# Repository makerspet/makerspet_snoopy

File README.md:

# Snoopy pet robot

An open-source 300mm DIY 3D-printable pet robot compatible with [Kaia.ai](https://kaia.ai) software [platform](https://github.com/kaiaai/).

Snoopy was designed in Fusion 360 in 05/2023 and printed using a Voron 2.4r2 350mm.

3D print, build, run and mod your own home pet robot! Please learn more at [Maker's Pet](https://makerspet.com).

## Features
- room mapping using a 360-degree laser distance sensor (ROS2-based).
- fully autonomous navigation (ROS2-based).
- code your character, skills (work in progress)
- 3D-printable, 300mm round base
- A smartphone or a 7" tablet acts as a color camera, head display.
- Arduino ESP32 micro-controller.
- optional: 2 bumpers, 4 bumper sensors, 5 cliff sensors.

## Assembly instructions video (Loki, Fido models)

## PC, firmware setup instructions video

## Bring-up instructions video

## 3D printing instructions

## Arduino ESP32 breakout board setup instructions

## Instructions and files
- 3D printing [STL](https://github.com/makerspet/3d_models/tree/main/snoopy_300mm/stl), [3MF](https://github.com/makerspet/3d_models/tree/main/snoopy_300mm/3mf)
- Arduino ESP32 [firmware](https://github.com/kaiaai/firmware)
- PC end user and developer [setup](https://github.com/kaiaai/docker)
- KiCad [schematic, PCB](https://github.com/makerspet/pcb)
- Software setup, configuration [instructions](https://www.youtube.com/playlist?list=PLOSXKDW70aR8SA16wTB0ou9ClKhv7micy)
- Fusion 360 3D CAD [design files](https://github.com/makerspet/3d_models/tree/main/snoopy_300mm/fusion360)
- ROS2 software mod [instructions](https://github.com/makerspet/makerspet_loki/tree/main/urdf)

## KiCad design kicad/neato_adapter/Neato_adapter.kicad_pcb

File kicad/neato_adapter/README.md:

# Adapter PCB for LDS02RR laser distance scanner

Connect Neato XV/Botvac LDS to Arduino to capture laser distance data.

This PCB implements PWM motor control for Neato XV/Botvac LDS. Find
sample Arduino ESP32 firmware code [here](https://github.com/kaiaai/LDS02RR_ESP32).

## Files
- [schematic PDF](output/Neato_adapter_schematic.pdf)
- [BoM .CSV](output/Neato_adapter_BOM.csv), [BoM .XML](output/Neato_adapter_BOM.xml)
- [Gerber .ZIP](output/Neato_adapter_gerber.zip)
- [3D model .STEP](output/Neato_adapter.step)
- KiCAD schematic, layout - in this folder

## Top

## Bottom

# Change log

## v0.1.0
- initial prototype
- optional LM2596 voltage regulator module provides 3.3V to motor

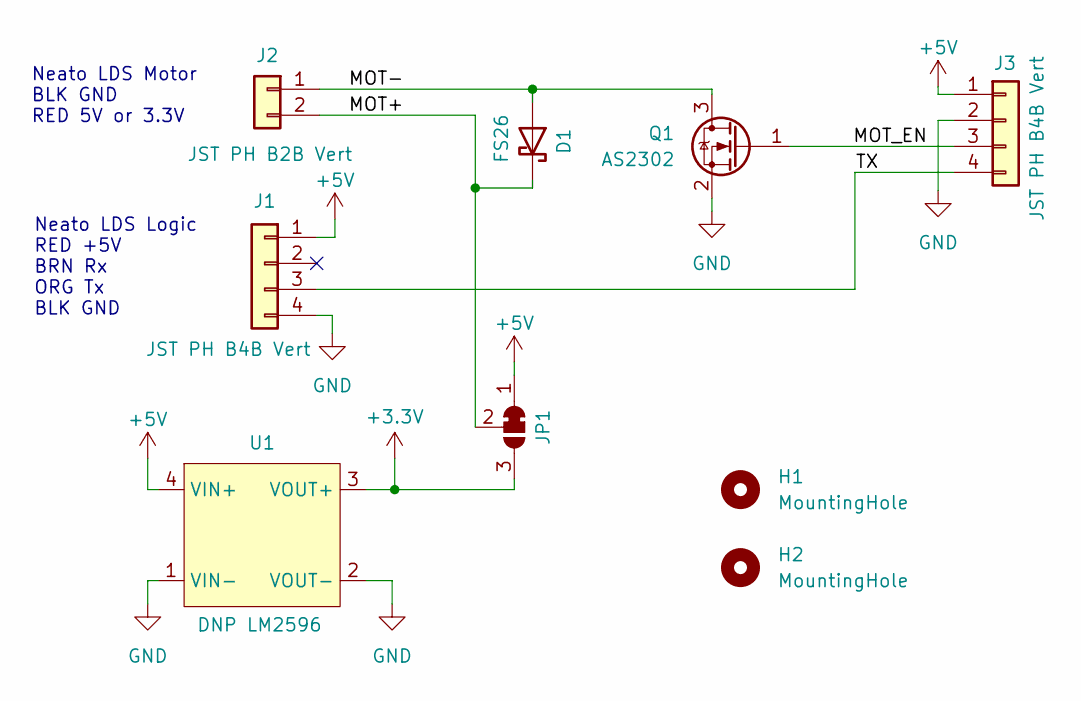
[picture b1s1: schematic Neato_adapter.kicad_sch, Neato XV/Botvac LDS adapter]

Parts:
D1: FS26; D_SOD-123F
H1, H2: MountingHole; MountingHole_3.2mm_M3
J1, J3: JST PH B4B Vert; JST_PH_B4B-PH-K_1x04_P2.00mm_Vertical
J2: JST PH B2B Vert; JST_PH_B2B-PH-K_1x02_P2.00mm_Vertical
JP1: SolderJumper_3_Bridged12; SolderJumper-3_P1.3mm_Bridged12_RoundedPad1.0x1.5mm_NumberL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
Q1: AS2302; SOT-23
U1: DNP LM2596; LM2596 Module

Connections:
+3.3V: JP1.3 (B), U1.3 (VOUT+)
+5V: J1.1, J3.1, JP1.1 (A), U1.4 (VIN+)
/MOT+: D1.1 (K), J2.2, JP1.2 (C)
/MOT-: D1.2 (A), J2.1, Q1.3 (D)
/MOT_EN: J3.3, Q1.1 (G)
/TX: J1.3, J3.4
GND: J1.4, J3.2, Q1.2 (S), U1.1 (VIN-), U1.2 (VOUT-)

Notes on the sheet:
Neato LDS Logic RED +5V BRN Rx ORG Tx BLK GND
Neato LDS Motor BLK GND RED 5V or 3.3V

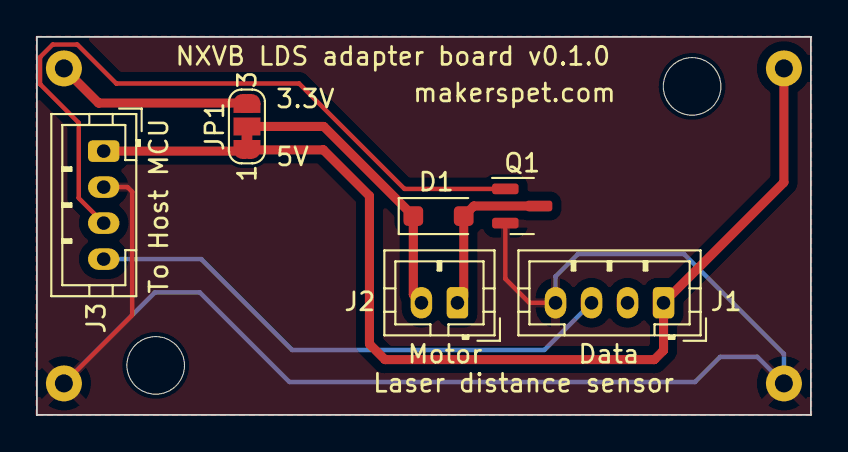
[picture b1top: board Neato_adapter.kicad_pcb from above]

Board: 2 copper layers, 43.0 x 21.0 mm, 9 parts (1 on the bottom side), 7 nets.

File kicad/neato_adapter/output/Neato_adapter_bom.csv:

"Source:","C:\Users\ilya\git\snoopy\kicad\neato_adapter\Neato_adapter.kicad_sch"
"Date:","1/16/2024 11:24:24 PM"
"Tool:","Eeschema 7.0.9"
"Generator:","C:\Program Files\KiCad\7.0\bin\scripting\plugins/bom_csv_grouped_by_value_with_fp.py"
"Component Count:","6"
"Ref","Qnty","Value","Cmp name","Footprint","Description","Vendor","DNP"
"D1","1","FS26","D_Schottky","Diode_SMD:D_SOD-123F","Schottky diode","",""
"J1, J3","2","JST PH B4B Vert","Conn_01x04","Connector_JST:JST_PH_B4B-PH-K_1x04_P2.00mm_Vertical","Generic connector, single row, 01x04, script generated (kicad-library-utils/schlib/autogen/connector/)","",""
"J2","1","JST PH B2B Vert","Conn_01x02","Connector_JST:JST_PH_B2B-PH-K_1x02_P2.00mm_Vertical","Generic connector, single row, 01x02, script generated (kicad-library-utils/schlib/autogen/connector/)","",""
"Q1","1","AS2302","BSS123","Package_TO_SOT_SMD:SOT-23","0.17A Id, 100V Vds, N-Channel MOSFET, SOT-23","",""
"U1","1","DNP LM2596","LM2596 Module","Makerspet:LM2596 Module","DC-DC voltage regulator module","",""

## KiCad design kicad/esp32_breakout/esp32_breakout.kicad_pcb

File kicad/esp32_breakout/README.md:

# Arduino ESP32 Breakout PCB for Maker's Pet robots

## Files
- [schematic PDF](output/esp32_breakout_schematic.pdf)
- [BoM .CSV](output/esp32_breakout_bom.csv), [BoM .XML](output/esp32_breakout_bom.xml)
- [Gerber .ZIP](output/esp32_breakout_gerber.zip)
- [3D model .STEP](output/esp32_breakout.step)
- KiCAD schematic, layout - in this folder

## Top

## Bottom

# Change log

## v1.1.0
- 3D-printed board enclosure to prevent accidental 24V shorts
- merged GPIO, US-100 sonar headers into a single 12-pin header

## v1.0.1
- fixed GPIO header footprint

## v1.0.0
- changed voltage regulator to LM2596 DC-DC module
  - unlike other low-cost DC-DC modules, LM2596 has built-in output current limit, short and thermal protection
  - LM2596 can accept up to 40V input as a measure for input overvoltage protection
  - Note that motors are not protected from overvoltage
- reduced the number of extension connectors to 2 from 3
  - for two Raspberry Pi Pico extension modules - one for the robot's head, one for the robot's body
- fixed extension interface I2C resistors
- replaced power connector with XT30 instead of Deans T-Plug
  - T-Plug requires uncomfortably too much insertion force
- added 24V input reverse polarity protection using a Schotki diode
- added 24 input overcurrent protection using a 2A one-time fuse
- removed support for LDS that don't control motor on/off
  - such LDS models are rare; this can be re-added later if needed
- added an ESP32 5V power supply protection Schottky diode
  - to prevent ESP32's USB back-charging the LM2596 voltage regulator
  - I don't believe this diode is necessary for LM2596 combined with built-in ESP32 Schottky diode, but let's have it just in case
- removed the 3-pin laser header and merged its GPIO to the GPIO connector
  - let's keep the ESP32 modules as a "platform" and put custom functionality on the Raspberry Pi Pico modules
  - customizing the ESP32 code to add custom functionality can easily slow down the ESP32 code that is optimized for speed and thus create issues
- changed the GPIO connector to single row from dual rows
  - to reduce the board size
  - I don't recommend using ESP32 GPIO because this requires modifying ESP32 code, which can easily slow down or break the ESP32 firmware.
    ESP32 is already pretty busy with ROS2 and WiFi low-latency communications.
  - please add custom functionality (sensors, servos, lights) to the Raspberry Pi Pico extension modules, not ESP32
- added US-100 ultrasonic range sensor
  - let's use US-100 instead of the popular HC-04 because HC-04 can "hang", sometimes requiring a power cycle.
    HC-04 performance varies depending on its manufacturer and some HC-04 modules are plain unusable.
    US-100 communicates with ESP32 using 9600 baud serial (less work for the ESP32 compared to HC-04)
    and offers a considerably better and consistent measurement quality. US-100 costs somewhat more compared to HC-04.
- fixed battery voltage sensing ADC resistor divider values
- removed battery charging connector
  - the charging connection depends on the battery BMS, therefore the charger/dock should connect to the battery instead of the board
- added silkscreens: makerspet.com, board name and version

## v0.1 PCB prototype
- Deans T-Plug type battery connector
- barrel-type battery charger connector
- US-100 ultrasonic distance sensor header
- laser pointer header
- miscellaneous unused GPIO header
- battery voltage sensing using ESP32 ADC
- PCB mounting holes
- 3 I2C extension connectors
- power-on switch
- LDS connector supporting a large variety of laser distance scanners, including those that don't control motor on/off
- fixed motors "kicking" during power-up
  - reassigned some motor control signals to ESP32 GPIO that do not toggle during ESP32 power-up boot
- mini560 Pro 5V DC-DC voltage regulator module

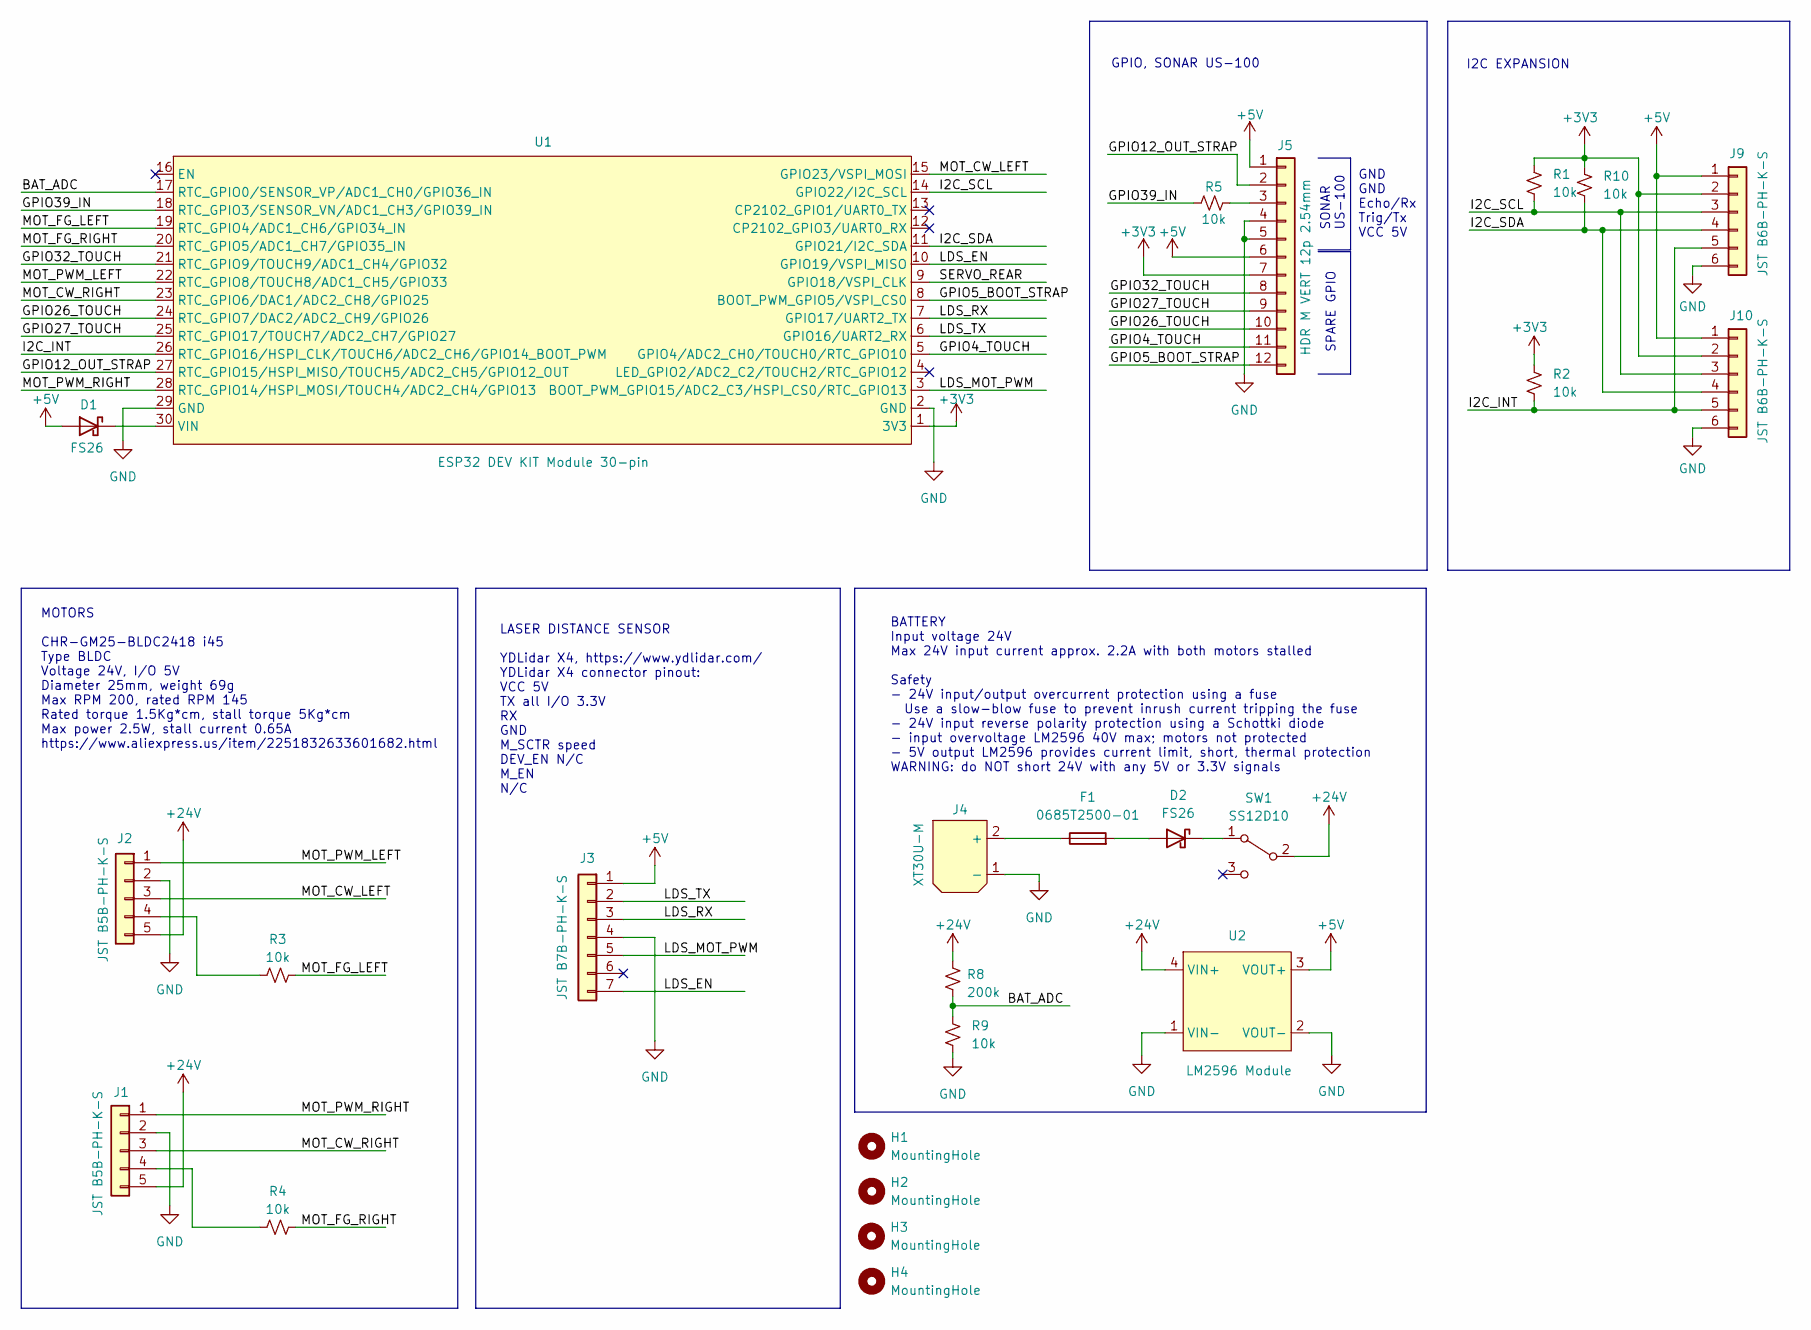
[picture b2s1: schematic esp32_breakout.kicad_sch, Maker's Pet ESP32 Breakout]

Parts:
D1, D2: FS26; D_SOD-123F
F1: 0685T2500-01; Fuse_1206_3216Metric
H1, H2, H3, H4: MountingHole; MountingHole_3.2mm_M3
J1, J2: JST B5B-PH-K-S; JST_PH_B5B-PH-K_1x05_P2.00mm_Vertical
J3: JST B7B-PH-K-S; JST_PH_B7B-PH-K_1x07_P2.00mm_Vertical
J4: XT30U-M; AMASS_XT30U-F_1x02_P5.0mm_Vertical
J5: HDR M VERT 12p 2.54mm; PinSocket_1x12_P2.54mm_Vertical
J9, J10: JST B6B-PH-K-S; JST_PH_B6B-PH-K_1x06_P2.00mm_Vertical
R1, R2, R3, R4, R5, R9, R10: 10k; R_0603_1608Metric
R8: 200k; R_0603_1608Metric
SW1: SS12D10; SWITCH
U1: ESP32 DEV KIT Module 30-pin; ESP-32
U2: LM2596 Module

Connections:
+3V3: J5.7, J9.2, J10.2, R1.1, R2.1, R10.1, U1.1 (3V3)
+5V: D1.2 (A), J3.1, J5.1, J5.6, J9.1, J10.1, U2.3 (VOUT+)
+24V: J1.5, J2.5, R8.2, SW1.2 (B), U2.4 (VIN+)
/BAT_ADC: R8.1, R9.2, U1.17 (RTC_GPIO0/SENSOR_VP/ADC1_CH0/GPIO36_IN)
/GPIO4_TOUCH: J5.11, U1.5 (GPIO4/ADC2_CH0/TOUCH0/RTC_GPIO10)
/GPIO5_BOOT_STRAP: J5.12, U1.8 (BOOT_PWM_GPIO5/VSPI_CS0)
/GPIO12_OUT_STRAP: J5.2, U1.27 (RTC_GPIO15/HSPI_MISO/TOUCH5/ADC2_CH5/GP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)
/GPIO26_TOUCH: J5.10, U1.24 (RTC_GPIO7/DAC2/ADC2_CH9/GPIO26)
/GPIO27_TOUCH: J5.9, U1.25 (RTC_GPIO17/TOUCH7/ADC2_CH7/GPIO27)
/GPIO32_TOUCH: J5.8, U1.21 (RTC_GPIO9/TOUCH9/ADC1_CH4/GPIO32)
/GPIO39_IN: R5.1, U1.18 (RTC_GPIO3/SENSOR_VN/ADC1_CH3/GPIO39_IN)
/I2C_INT: J9.5, J10.5, R2.2, U1.26 (RTC_GPIO16/HSPI_CLK/TOUCH6/ADC2_CH6/GPI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)
/I2C_SCL: J9.3, J10.3, R1.2, U1.14 (GPIO22/I2C_SCL)
/I2C_SDA: J9.4, J10.4, R10.2, U1.11 (GPIO21/I2C_SDA)
/LDS_EN: J3.7, U1.10 (GPIO19/VSPI_MISO)
/LDS_MOT_PWM: J3.5, U1.3 (BOOT_PWM_GPIO15/ADC2_C3/HSPI_CS0/RTC_GP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)
/LDS_RX: J3.3, U1.7 (GPIO17/UART2_TX)
/LDS_TX: J3.2, U1.6 (GPIO16/UART2_RX)
/MOT_CW_LEFT: J2.3, U1.15 (GPIO23/VSPI_MOSI)
/MOT_CW_RIGHT: J1.3, U1.23 (RTC_GPIO6/DAC1/ADC2_CH8/GPIO25)
/MOT_FG_LEFT: R3.1, U1.19 (RTC_GPIO4/ADC1_CH6/GPIO34_IN)
/MOT_FG_RIGHT: R4.1, U1.20 (RTC_GPIO5/ADC1_CH7/GPIO35_IN)
/MOT_PWM_LEFT: J2.1, U1.22 (RTC_GPIO8/TOUCH8/ADC1_CH5/GPIO33)
/MOT_PWM_RIGHT: J1.1, U1.28 (RTC_GPIO14/HSPI_MOSI/TOUCH4/ADC2_CH4/GP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)
/SERVO_REAR: U1.9 (GPIO18/VSPI_CLK)
GND: J1.2, J2.2, J3.4, J4.1 (-), J5.4, J5.5, J9.6, J10.6, R9.1, U1.2 (GND), U1.29 (GND), U2.1 (VIN-), U2.2 (VOUT-)
unnamed: D1.1 (K), U1.30 (VIN)
unnamed: D2.2 (A), F1.2
unnamed: D2.1 (K), SW1.1 (A)
unnamed: J1.4, R4.2
unnamed: J2.4, R3.2
unnamed: F1.1, J4.2 (+)
unnamed: J5.3, R5.2

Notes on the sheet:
SONAR US-100
GND GND Echo/Rx Trig/Tx VCC 5V
SPARE GPIO
GPIO, SONAR US-100
I2C EXPANSION
BATTERY Input voltage 24V Max 24V input current approx. 2.2A with both motors stalled Safety - 24V input/output overcurrent protection using a fuse Use a slow-blow fuse to prevent inrush current tripping the fuse - 24V input reverse polarity protection using a Schottki diode - input overvoltage LM2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
MOTORS CHR-GM25-BLDC2418 i45 Type BLDC Voltage 24V, I/O 5V Diameter 25mm, weight 69g Max RPM 200, rated RPM 145 Rated torque 1.5Kg*cm, stall torque 5Kg*cm Max power 2.5W, stall current 0.65A https://www.aliexpress.us/item/2251832633601682.html
LASER DISTANCE SENSOR YDLidar X4, https://www.ydlidar.com/ YDLidar X4 connector pinout: VCC 5V TX all I/O 3.3V RX GND M_SCTR speed DEV_EN N/C M_EN N/C

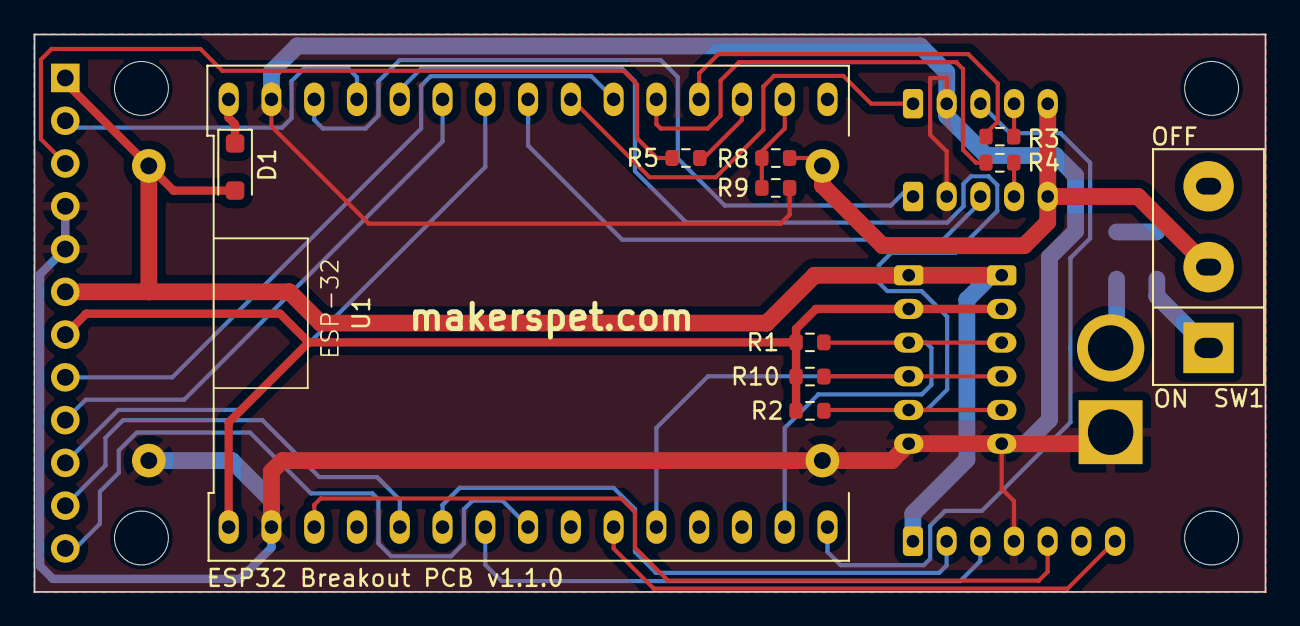
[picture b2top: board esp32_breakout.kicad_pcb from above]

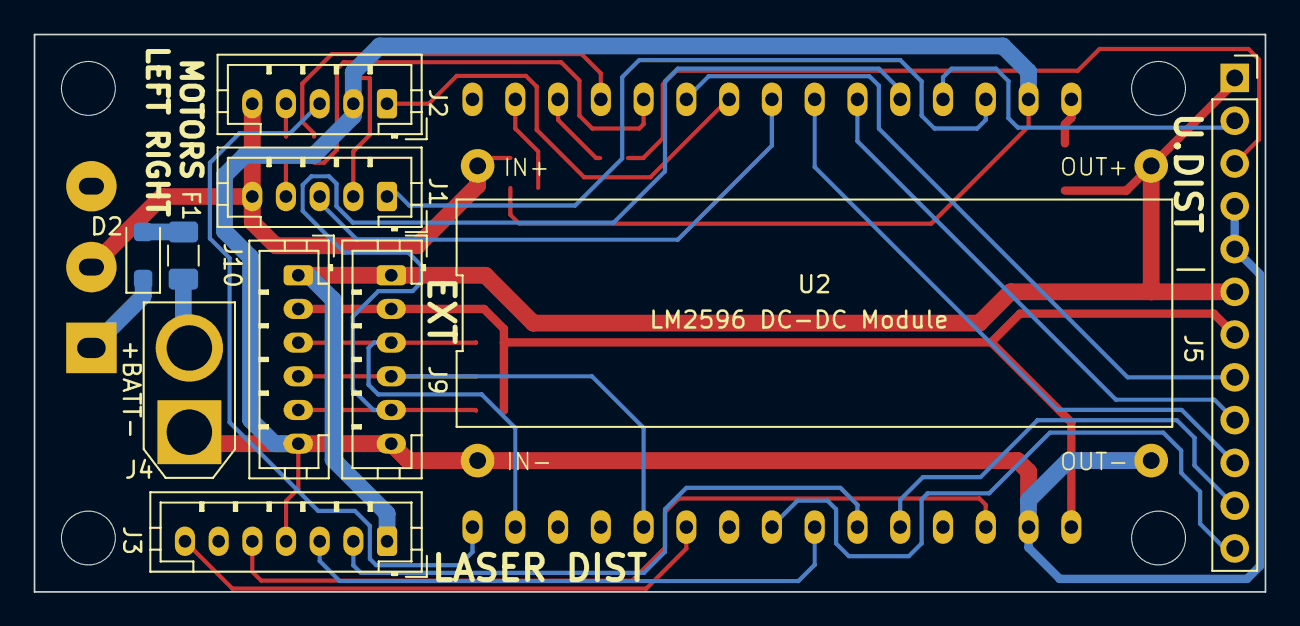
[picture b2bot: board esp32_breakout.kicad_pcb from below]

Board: 2 copper layers, 73.1 x 33.1 mm, 25 parts (10 on the bottom side), 32 nets.

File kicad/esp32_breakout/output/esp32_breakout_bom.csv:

"Source:","C:\Users\ilya\git\snoopy\kicad\esp32_breakout\esp32_breakout.kicad_sch"
"Date:","12/30/2023 9:12:20 PM"
"Tool:","Eeschema 7.0.9"
"Generator:","C:\Program Files\KiCad\7.0\bin\scripting\plugins/bom_csv_grouped_by_value_with_fp.py"
"Component Count:","25"
"Ref","Qnty","Value","Cmp name","Footprint","Description","Vendor","DNP"
"D1, D2","2","FS26","D_Schottky","Diode_SMD:D_SOD-123F","Schottky diode","",""
"F1","1","0685T2500-01","Fuse","Fuse:Fuse_1206_3216Metric","Fuse","",""
"H1, H2, H3, H4","4","MountingHole","MountingHole","MountingHole:MountingHole_3.2mm_M3","Mounting Hole without connection","",""
"J1, J2","2","JST B5B-PH-K-S","Conn_01x05","Connector_JST:JST_PH_B5B-PH-K_1x05_P2.00mm_Vertical","Generic connector, single row, 01x05, script generated (kicad-library-utils/schlib/autogen/connector/)","",""
"J3","1","JST B7B-PH-K-S","Conn_01x07","Connector_JST:JST_PH_B7B-PH-K_1x07_P2.00mm_Vertical","Generic connector, single row, 01x07, script generated (kicad-library-utils/schlib/autogen/connector/)","",""
"J4","1","XT30U-M","XT30UPB-M","Makerspet:AMASS_XT30U-F_1x02_P5.0mm_Vertical","","",""
"J5","1","HDR M VERT 12p 2.54mm","Conn_01x12","Connector_PinSocket_2.54mm:PinSocket_1x12_P2.54mm_Vertical","Generic connector, single row, 01x12, script generated (kicad-library-utils/schlib/autogen/connector/)","",""
"J9, J10","2","JST B6B-PH-K-S","Conn_01x06","Connector_JST:JST_PH_B6B-PH-K_1x06_P2.00mm_Vertical","Generic connector, single row, 01x06, script generated (kicad-library-utils/schlib/autogen/connector/)","",""
"R1, R2, R3, R4, R5, R9, R10","7","10k","R_Small_US","Resistor_SMD:R_0603_1608Metric","Resistor, small US symbol","",""
"R8","1","200k","R_Small_US","Resistor_SMD:R_0603_1608Metric","Resistor, small US symbol","",""
"SW1","1","SS12D10","SW_SPDT","Makerspet:SWITCH","Switch, single pole double throw","",""
"U1","1","ESP32 DEV KIT Module 30-pin","ESP32-DOIT-V1","Makerspet:ESP-32","","",""
"U2","1","LM2596 Module","DC-DC Module","Makerspet:LM2596 Module","DC-DC voltage regulator module","",""

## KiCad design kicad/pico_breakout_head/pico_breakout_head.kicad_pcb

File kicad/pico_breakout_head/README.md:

# Raspberry Pi Pico Head Breakout PCB for Maker's Pet robots

## Files
- [schematic PDF](output/pico_breakout_head_schematic.pdf)
- [BoM .CSV](output/pico_breakout_head_bom.csv), [BoM .XML](output/pico_breakout_head_bom.xml)
- [Gerber .ZIP](output/pico_breakout_head_gerber.zip)
- [3D model .STEP](output/pico_breakout_head.step)
- KiCAD schematic, layout - in this folder

## Top

## Bottom

# Change log

## v0.2.0 PCB prototype
- fan N-MOSFET fix
- removed fan diode
  - unnecessary for such a small motor

## v0.1.1 PCB prototype
- use same diode components
- removed fan MOSFET gate resistor

## v0.1 PCB prototype
- I2C host interface connector
- fan connector
- connector for 3 servos
  - left and right ears plus one extra
- touch connector with 4 segments

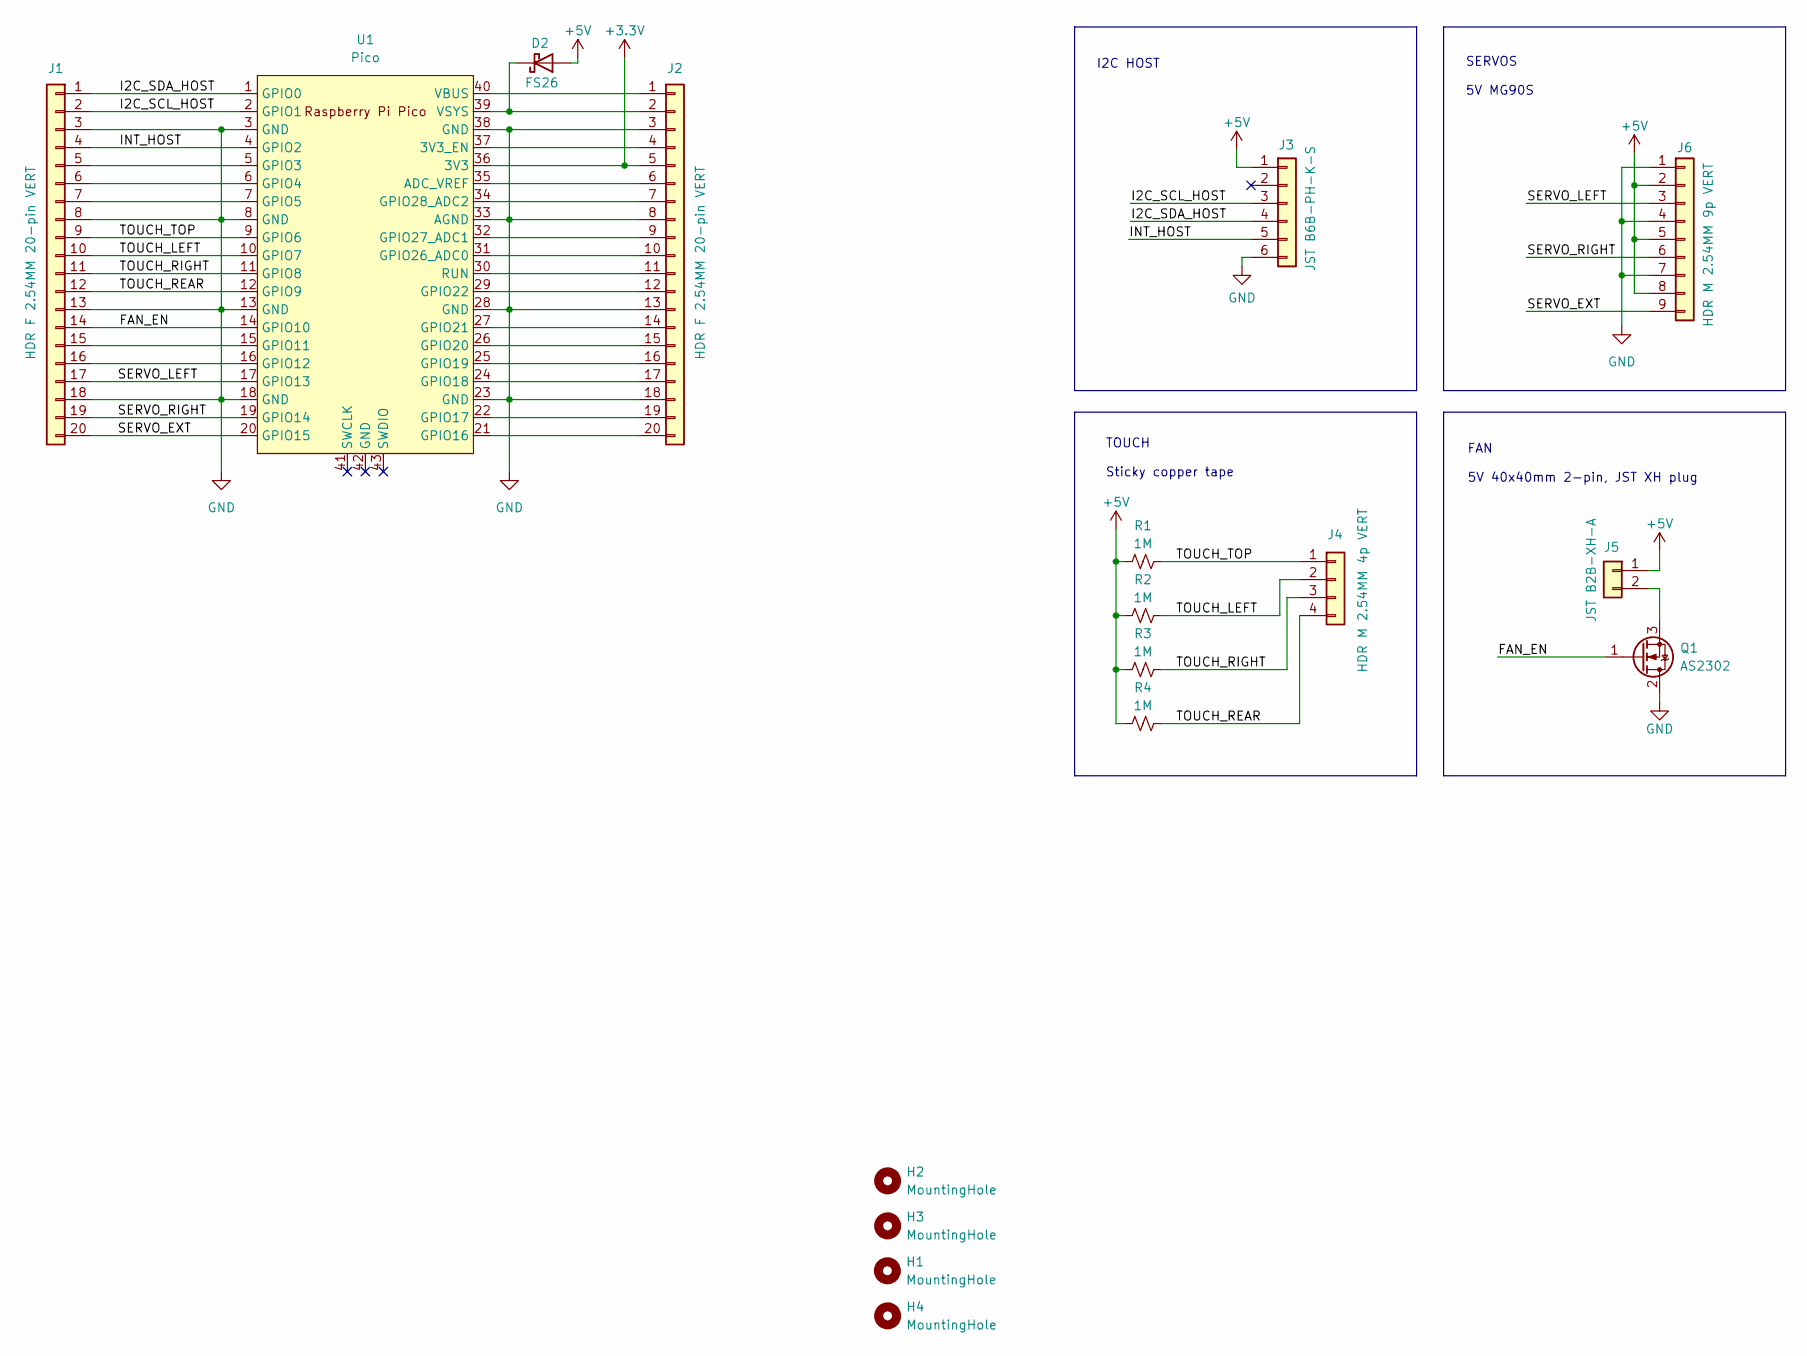
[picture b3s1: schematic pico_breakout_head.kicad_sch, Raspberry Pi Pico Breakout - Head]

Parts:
D2: FS26; D_SOD-123F
H1, H2, H3, H4: MountingHole; MountingHole_3.2mm_M3
J1, J2: HDR F 2.54MM 20-pin VERT; PinSocket_1x20_P2.54mm_Vertical
J3: JST B6B-PH-K-S; JST_PH_B6B-PH-K_1x06_P2.00mm_Vertical
J4: HDR M 2.54MM 4p VERT; PinSocket_1x04_P2.54mm_Vertical
J5: JST B2B-XH-A; JST_XH_B2B-XH-A_1x02_P2.50mm_Vertical
J6: HDR M 2.54MM 9p VERT; PinSocket_1x09_P2.54mm_Vertical
Q1: AS2302; SOT-23
R1, R2, R3, R4: 1M; R_0603_1608Metric
U1: Pico; RPi_Pico_SMD_TH

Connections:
+3.3V: J2.5, U1.36 (3V3)
+5V: D2.2 (A), J3.1, J5.1, J6.2, J6.5, J6.8, R1.2, R2.2, R3.2, R4.2
/FAN_EN: J1.14, Q1.1 (G), U1.14 (GPIO10)
/I2C_SCL_HOST: J1.2, J3.3, U1.2 (GPIO1)
/I2C_SDA_HOST: J1.1, J3.4, U1.1 (GPIO0)
/INT_HOST: J1.4, J3.5, U1.4 (GPIO2)
/SERVO_EXT: J1.20, J6.9, U1.20 (GPIO15)
/SERVO_LEFT: J1.17, J6.3, U1.17 (GPIO13)
/SERVO_RIGHT: J1.19, J6.6, U1.19 (GPIO14)
/TOUCH_LEFT: J1.10, J4.2, R2.1, U1.10 (GPIO7)
/TOUCH_REAR: J1.12, J4.4, R4.1, U1.12 (GPIO9)
/TOUCH_RIGHT: J1.11, J4.3, R3.1, U1.11 (GPIO8)
/TOUCH_TOP: J1.9, J4.1, R1.1, U1.9 (GPIO6)
GND: J1.3, J1.8, J1.13, J1.18, J2.3, J2.8, J2.13, J2.18, J3.6, J6.1, J6.4, J6.7, Q1.2 (D), U1.3 (GND), U1.8 (GND), U1.13 (GND), U1.18 (GND), U1.23 (GND), U1.28 (GND), U1.33 (AGND), U1.38 (GND)
unnamed: D2.1 (K), J2.2, U1.39 (VSYS)
unnamed: J1.5, U1.5 (GPIO3)
unnamed: J1.6, U1.6 (GPIO4)
unnamed: J1.7, U1.7 (GPIO5)
unnamed: J1.15, U1.15 (GPIO11)
unnamed: J1.16, U1.16 (GPIO12)
unnamed: J2.1, U1.40 (VBUS)
unnamed: J2.4, U1.37 (3V3_EN)
unnamed: J2.6, U1.35 (ADC_VREF)
unnamed: J2.7, U1.34 (GPIO28_ADC2)
unnamed: J2.9, U1.32 (GPIO27_ADC1)
unnamed: J2.10, U1.31 (GPIO26_ADC0)
unnamed: J2.11, U1.30 (RUN)
unnamed: J2.12, U1.29 (GPIO22)
unnamed: J2.14, U1.27 (GPIO21)
unnamed: J2.15, U1.26 (GPIO20)
unnamed: J2.16, U1.25 (GPIO19)
unnamed: J2.17, U1.24 (GPIO18)
unnamed: J2.19, U1.22 (GPIO17)
unnamed: J2.20, U1.21 (GPIO16)
unnamed: J5.2, Q1.3 (S)

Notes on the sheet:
SERVOS 5V MG90S
FAN 5V 40x40mm 2-pin, JST XH plug
I2C HOST
TOUCH Sticky copper tape

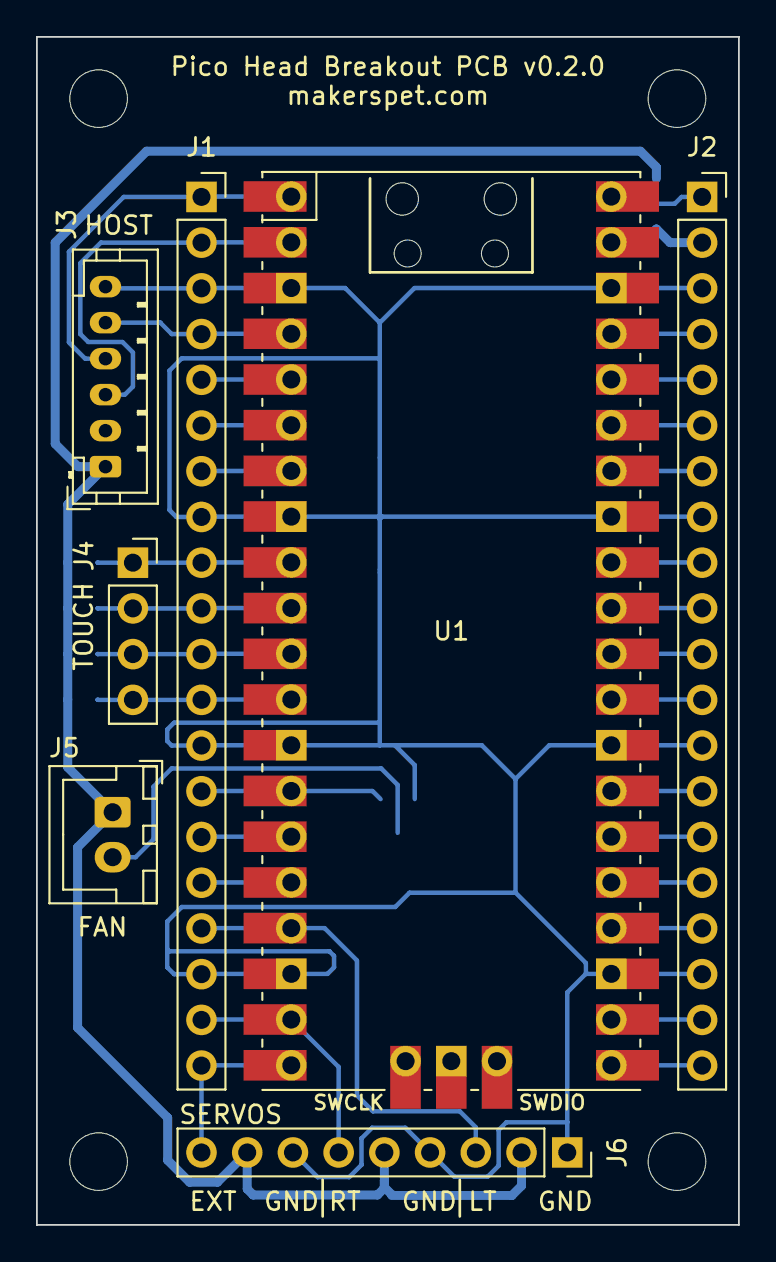
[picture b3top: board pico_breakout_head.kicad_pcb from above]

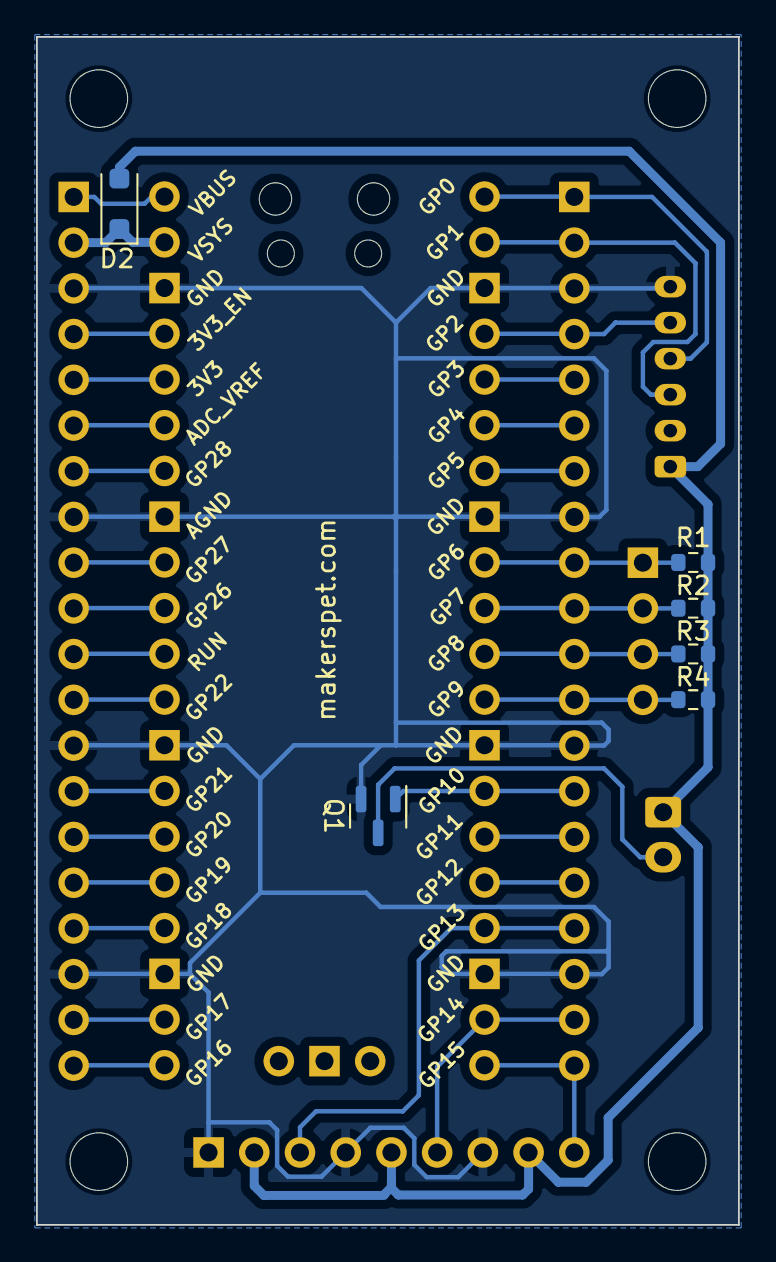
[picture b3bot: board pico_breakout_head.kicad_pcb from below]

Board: 2 copper layers, 39.0 x 66.0 mm, 17 parts (6 on the bottom side), 35 nets.

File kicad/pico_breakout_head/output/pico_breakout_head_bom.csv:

"Source:","C:\Users\ilya\git\snoopy\kicad\pico_breakout_head\pico_breakout_head.kicad_sch"
"Date:","12/26/2023 1:05:24 AM"
"Tool:","Eeschema 7.0.9"
"Generator:","C:\Program Files\KiCad\7.0\bin\scripting\plugins/bom_csv_grouped_by_value_with_fp.py"
"Component Count:","17"
"Ref","Qnty","Value","Cmp name","Footprint","Description","Vendor","DNP"
"D2","1","FS26","D_Schottky","Diode_SMD:D_SOD-123F","Schottky diode","",""
"H1, H2, H3, H4","4","MountingHole","MountingHole","MountingHole:MountingHole_3.2mm_M3","Mounting Hole without connection","",""
"J1, J2","2","HDR F 2.54MM 20-pin VERT","Conn_01x20","Connector_PinSocket_2.54mm:PinSocket_1x20_P2.54mm_Vertical","Generic connector, single row, 01x20, script generated (kicad-library-utils/schlib/autogen/connector/)","",""
"J3","1","JST B6B-PH-K-S","Conn_01x06","Connector_JST:JST_PH_B6B-PH-K_1x06_P2.00mm_Vertical","Generic connector, single row, 01x06, script generated (kicad-library-utils/schlib/autogen/connector/)","",""
"J4","1","HDR M 2.54MM 4p VERT","Conn_01x04","Connector_PinSocket_2.54mm:PinSocket_1x04_P2.54mm_Vertical","Generic connector, single row, 01x04, script generated (kicad-library-utils/schlib/autogen/connector/)","",""
"J5","1","JST B2B-XH-A","Conn_01x02","Connector_JST:JST_XH_B2B-XH-A_1x02_P2.50mm_Vertical","Generic connector, single row, 01x02, script generated (kicad-library-utils/schlib/autogen/connector/)","",""
"J6","1","HDR M 2.54MM 9p VERT","Conn_01x09","Connector_PinSocket_2.54mm:PinSocket_1x09_P2.54mm_Vertical","Generic connector, single row, 01x09, script generated (kicad-library-utils/schlib/autogen/connector/)","",""
"Q1","1","AS2302","AS2302","Package_TO_SOT_SMD:SOT-23","3A Id, 20V Vds, N-Channel MOSFET, SOT-23","",""
"R1, R2, R3, R4","4","1M","R_Small_US","Resistor_SMD:R_0603_1608Metric","Resistor, small US symbol","",""
"U1","1","Pico","Pico","Makerspet:RPi_Pico_SMD_TH","","",""

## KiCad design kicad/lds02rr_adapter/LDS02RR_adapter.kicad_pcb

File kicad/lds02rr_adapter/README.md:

# Adapter PCB for LDS02RR laser distance scanner

Connect LDS02RR to Arduino to capture laser distance data.

This PCB implements PWM motor control for LDS02RR. Find
sample Arduino ESP32 firmware code [here](https://github.com/kaiaai/LDS02RR_ESP32).

## Files
- [schematic PDF](output/LDS02RR_adapter_schematic.pdf)
- [BoM .CSV](output/LDS02RR_adapter_BOM.csv), [BoM .XML](output/LDS02RR_adapter_BOM.xml)
- [Gerber .ZIP](output/LDS02RR_adapter_gerber.zip)
- [3D model .STEP](output/LDS02RR_adapter.step)
- KiCAD schematic, layout - in this folder

## Top

## Bottom

# Change log

## v0.1.0
- initial prototype
- PCB inserts into LDS02RR connector
- 4-pin JST PH connector - 5V, GND, LDS motor PWM, LDS TX

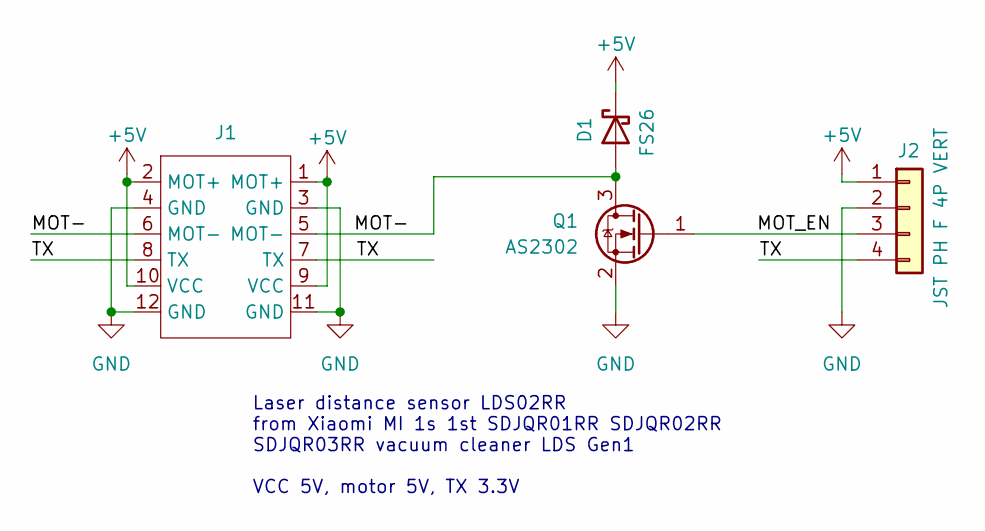
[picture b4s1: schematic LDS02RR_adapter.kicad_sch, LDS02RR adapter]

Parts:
D1: FS26; D_SOD-123F
J1: LDS02RR_FPC12
J2: JST PH F 4P VERT; JST_PH_B4B-PH-K_1x04_P2.00mm_Vertical
Q1: AS2302; SOT-23

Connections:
+5V: D1.1 (K), J1.1 (MOT+), J1.2 (MOT+), J1.9 (VCC), J1.10 (VCC), J2.1
/MOT-: D1.2 (A), J1.5 (MOT-), J1.6 (MOT-), Q1.3 (D)
/MOT_EN: J2.3, Q1.1 (G)
/TX: J1.7 (TX), J1.8 (TX), J2.4
GND: J1.3 (GND), J1.4 (GND), J1.11 (GND), J1.12 (GND), J2.2, Q1.2 (S)

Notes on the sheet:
Laser distance sensor LDS02RR from Xiaomi MI 1s 1st SDJQR01RR SDJQR02RR SDJQR03RR vacuum cleaner LDS Gen1 VCC 5V, motor 5V, TX 3.3V

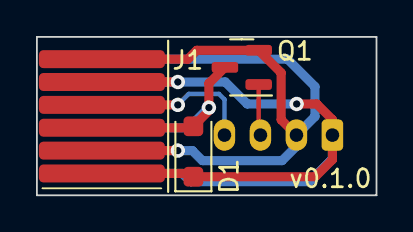
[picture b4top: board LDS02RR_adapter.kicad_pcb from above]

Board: 2 copper layers, 18.9 x 8.8 mm, 4 parts (1 on the bottom side), 5 nets.

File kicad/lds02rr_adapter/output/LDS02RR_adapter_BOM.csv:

"Source:","C:\Users\ilya\git\snoopy\kicad\lds02rr_adapter\LDS02RR_adapter.kicad_sch"
"Date:","12/21/2023 7:05:36 PM"
"Tool:","Eeschema 7.0.9"
"Generator:","C:\Program Files\KiCad\7.0\bin\scripting\plugins/bom_csv_grouped_by_value_with_fp.py"
"Component Count:","4"
"Ref","Qnty","Value","Cmp name","Footprint","Description","Vendor","DNP"
"D1","1","FS26","D_Schottky","Diode_SMD:D_SOD-123F","Schottky diode","",""
"J1","1","~","LDS02RR","Makerspet:LDS02RR_FPC12","Xiaomi Roborock laser distance sensor","",""
"J2","1","JST PH F 4P VERT","Conn_01x04","Connector_JST:JST_PH_B4B-PH-K_1x04_P2.00mm_Vertical","Generic connector, single row, 01x04, script generated (kicad-library-utils/schlib/autogen/connector/)","",""
"Q1","1","AS2302","BSS123","Package_TO_SOT_SMD:SOT-23","0.17A Id, 100V Vds, N-Channel MOSFET, SOT-23","",""

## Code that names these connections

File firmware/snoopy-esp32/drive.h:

#ifndef KAIA_DRIVE_H_
#define KAIA_DRIVE_H_

#include <math.h>

#include <Arduino.h>
#include <PID_v1.h>

#define PID_UPDATE_PERIOD          0.03 // default in seconds
#define PID_KP_WHEEL               0.001 // 0.003 P_ON_E
#define PID_KI_WHEEL               0.001 // 0.0002
#define PID_KD_WHEEL               0
#define PID_MODE                   (P_ON_M) // P_ON_E

#define PWM_FREQ                   20000 // 15..25KHz
#define PWM_BITS                   10
#define PWM_MAX                    (1<<10)  // 1024

#define MOTOR_LEFT                 0
#define MOTOR_RIGHT                1
#define MOTOR_COUNT                (MOTOR_RIGHT+1)

#define MOT_PWM_LEFT_PIN           33
#define MOT_CW_LEFT_PIN            32
#define MOT_FG_LEFT_PIN            34

#define MOT_PWM_RIGHT_PIN          13 
#define MOT_CW_RIGHT_PIN           25
#define MOT_FG_RIGHT_PIN           27

#define MOTOR_WHEEL_MAX_RPM        180 // rated 145, no-load 200

// 1:45 gear ratio * 6 pulses/cycle * 2 edges
#define WHEEL_ENCODER_TPR         (45.0*6*2) // ticks per revolution

#define FLIP_ROTATION              true

typedef void (*logFuncT)(char*);

class DriveController
{
  public:
    DriveController();
    void initOnce(logFuncT logFunc);
    bool setRPM(unsigned char motorID, float rpm);
    void resetEncoders();
    void update();
    float getShaftAngle(unsigned char motorID);
    void setPIDUpdatePeriod(unsigned char motorID, float period);
    void setPWM(unsigned char motorID, float pwm);
    void enablePID(unsigned char motorID, bool en);
    void setMaxRPM(unsigned char motorID, float rpm);
    void setEncoderTPR(unsigned char motorID, float tpr);

    void setKp(unsigned char motorID, float k);
    void setKi(unsigned char motorID, float k);
    void setKd(unsigned char motorID, float k);
    void setProportionalMode(unsigned char motorID, bool onMeasurement);
    void setPWMFreq(unsigned char motorID, unsigned short int freq);
    void enable(bool enabled);
    bool isEnabled();

    double getCurrentRPM(unsigned char motorID);
    double getTargetRPM(unsigned char motorID);
    float getCurrentPWM(unsigned char motorID);
    float getMaxRPM(unsigned char motorID);

  private:
    PID *pid[MOTOR_COUNT];
    float kp[MOTOR_COUNT];
    float ki[MOTOR_COUNT];
    float kd[MOTOR_COUNT];
    unsigned int pidUpdatePeriodUs;
    unsigned long tickSampleTimePrev;
    unsigned long tickSampleTimeDelta;

    double targetRPM[MOTOR_COUNT];
    double measuredRPM[MOTOR_COUNT];
    double pidPWM[MOTOR_COUNT];
    int PWM[MOTOR_COUNT];

    double ticksPerMicroSecToRPM[MOTOR_COUNT];
    long int encDelta[MOTOR_COUNT];
    float maxRPM[MOTOR_COUNT];
    float encoderTPR[MOTOR_COUNT];
    long int encPrev[MOTOR_COUNT];
    bool setPointHasChanged[MOTOR_COUNT];

    unsigned short int pwmFreq[MOTOR_COUNT];
    unsigned char pwmPin[MOTOR_COUNT];
    unsigned char cwPin[MOTOR_COUNT];

    bool enabled;
    bool switchingCw[MOTOR_COUNT];
    logFuncT logDebug;
};

extern DriveController drive;

#endif

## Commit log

2023-09-03 Moved from kaia.ai
2023-09-07 Repo reord, added ROS2 software
2023-09-07 Firmware
2023-09-08 hardware folder
2023-09-08 Cleanup
2023-09-08 Package rename
2023-09-08 Tweak
2023-09-13 Fixed Fusion360 name
2023-09-14 Schematic, BOM
2023-09-14 T Plug fix
2023-09-16 Renamed package
2023-09-17 Renamed packages
2023-09-19 URDF fix
2023-09-21 Gazebo rviz cleanup
2023-09-21 Self drive stuck
2023-09-22 Self drive fix
2023-09-22 Rviz odom keep
2023-09-22 Turn off ray vis
2023-09-22 Move urdf2sdf.sh
2023-09-22 Moved out clone script
2023-09-22 SDF fix
2023-09-22 Rviz mesh fix
2023-09-22 Regenerated SDF
2023-09-25 Destination IP, port; kaiaai naming
2023-09-26 Destination IP, port
2023-09-26 Telem pub period stats
2023-09-26 Undo drive enable
2023-09-26 enableLdsMotor() rename
2023-09-27 Keep retrying Micro-ROS
2023-09-27 Checked transports error, no use
2023-09-27 Nicer error loop
2023-09-27 Max motor teleop speed
2023-09-27 Reversed left motor
2023-09-28 Teleop large step
2023-09-28 WiFi manager tweak
2023-09-28 Teleop defaults
2023-09-28 Motors seem to work
2023-09-28 URDF wheel base fix
2023-09-28 URDF base fix
2023-09-28 Telem lds frame rename
2023-09-28 Teleop params cleanup
2023-09-28 Odom sign fix; stop without WiFi
2023-09-28 Fix world frame
2023-09-29 URDF base_scan fix
2023-09-29 odom fix
2023-09-29 Servos, dock, pulldowns
2023-09-30 Cartographer, nav yaml
2023-09-30 Home map
2023-10-30 PID library
2023-10-30 KiCad PCB work-in-progress
2023-11-01 Node name
2023-11-01 Email fix
2023-11-01 monitor_robot.rviz
2023-11-03 Quarter sphere head
2023-11-03 Quarter sphere cuts
2023-11-03 URDF cmd_vel fix
2023-11-03 Battery weight
2023-11-04 robot.urdf.xacro
2023-11-04 Undo hw,fw folders
2023-11-06 Simpler fw models
2023-11-07 living_room map
2023-11-07 No map
2023-11-07 Nav2 iron YAML
2023-11-15 KiCad PCB schematic
2023-11-15 Schematic WIP
2023-11-16 Fix broken fw; ESP32 schematic
2023-11-16 Layout DRC pass
2023-11-17 PCB gerber
2023-11-18 FW LDS error clarified
2023-11-18 FW fix max speed drift
2023-11-23 Copyright
2023-11-23 Restore humble nav.yaml
2023-11-23 3D printing vid
2023-12-01 Schematic, BOM R9 fix
2023-12-14 PCB updated to product
2023-12-15 Pico head WiP
2023-12-15 5V OR Schottky diode
2023-12-15 Pico head breakout layout start
2023-12-16 ESP32 breakout v1.0
2023-12-16 Raspberry Pi Pico head extension PCB proto
2023-12-17 KiCAD bugfix?
2023-12-17 Gerber fix
2023-12-18 Socket header
2023-12-18 ESP32 PCB README files
2023-12-19 ESP32 board v1.1
2023-12-19 PCB image fix
2023-12-19 PCB image fix again
2023-12-22 LDS02RR adapter PCB
2023-12-22 Reverted ESP32 PCB to v1
2023-12-22 Pico head PCB 0.1.1
2023-12-24 Footprint fix
2023-12-26 Alt fuse; fan fix
2023-12-29 ESP32 PCB v1.1.0
2023-12-29 Single GPIO header
2023-12-31 PCB hole, sonar tweaks
2024-01-12 LDS02RR PCB README
2024-01-21 Neato LDS adapter schematic
2024-01-21 Neato adapter PCB Gerber
2024-01-21 Firmware release
2024-01-21 Redo iron off humble
2024-01-23 Moved PCB to dedicated repo
2024-01-28 YDLIDAR X2 support
2024-01-28 Firmware moved to kaiaai/firmware repo
2024-01-29 YDLIDAR X3 PRO
2024-02-02 Neato XV11
2024-02-04 telem params delta
2024-02-15 Moved 3D models to a separate repo
2024-02-15 Updated links
2025-10-04 gz camera works
